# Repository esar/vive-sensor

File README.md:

# vive-sensor
A small PCB implementing this circuit by Alan Yates: https://twitter.com/vk2zay/status/716137353278939136

This circuit amplifies, band-pass filters, and envelope detects the signal received from Vive lighthouse base stations. The output is a clean 3.3V pulse. 

It performs a similar function to the off-the-shelf TS3633-CM1 sensor from Triad Semiconductor, but for a fraction of the cost (and the expense of assembly).

The board is populate on both sides and measures 10mm x 16mm.
The photo-diode can either be a through-hole part mounted as shown in the photo below, or a surface-mount part parallel to the board

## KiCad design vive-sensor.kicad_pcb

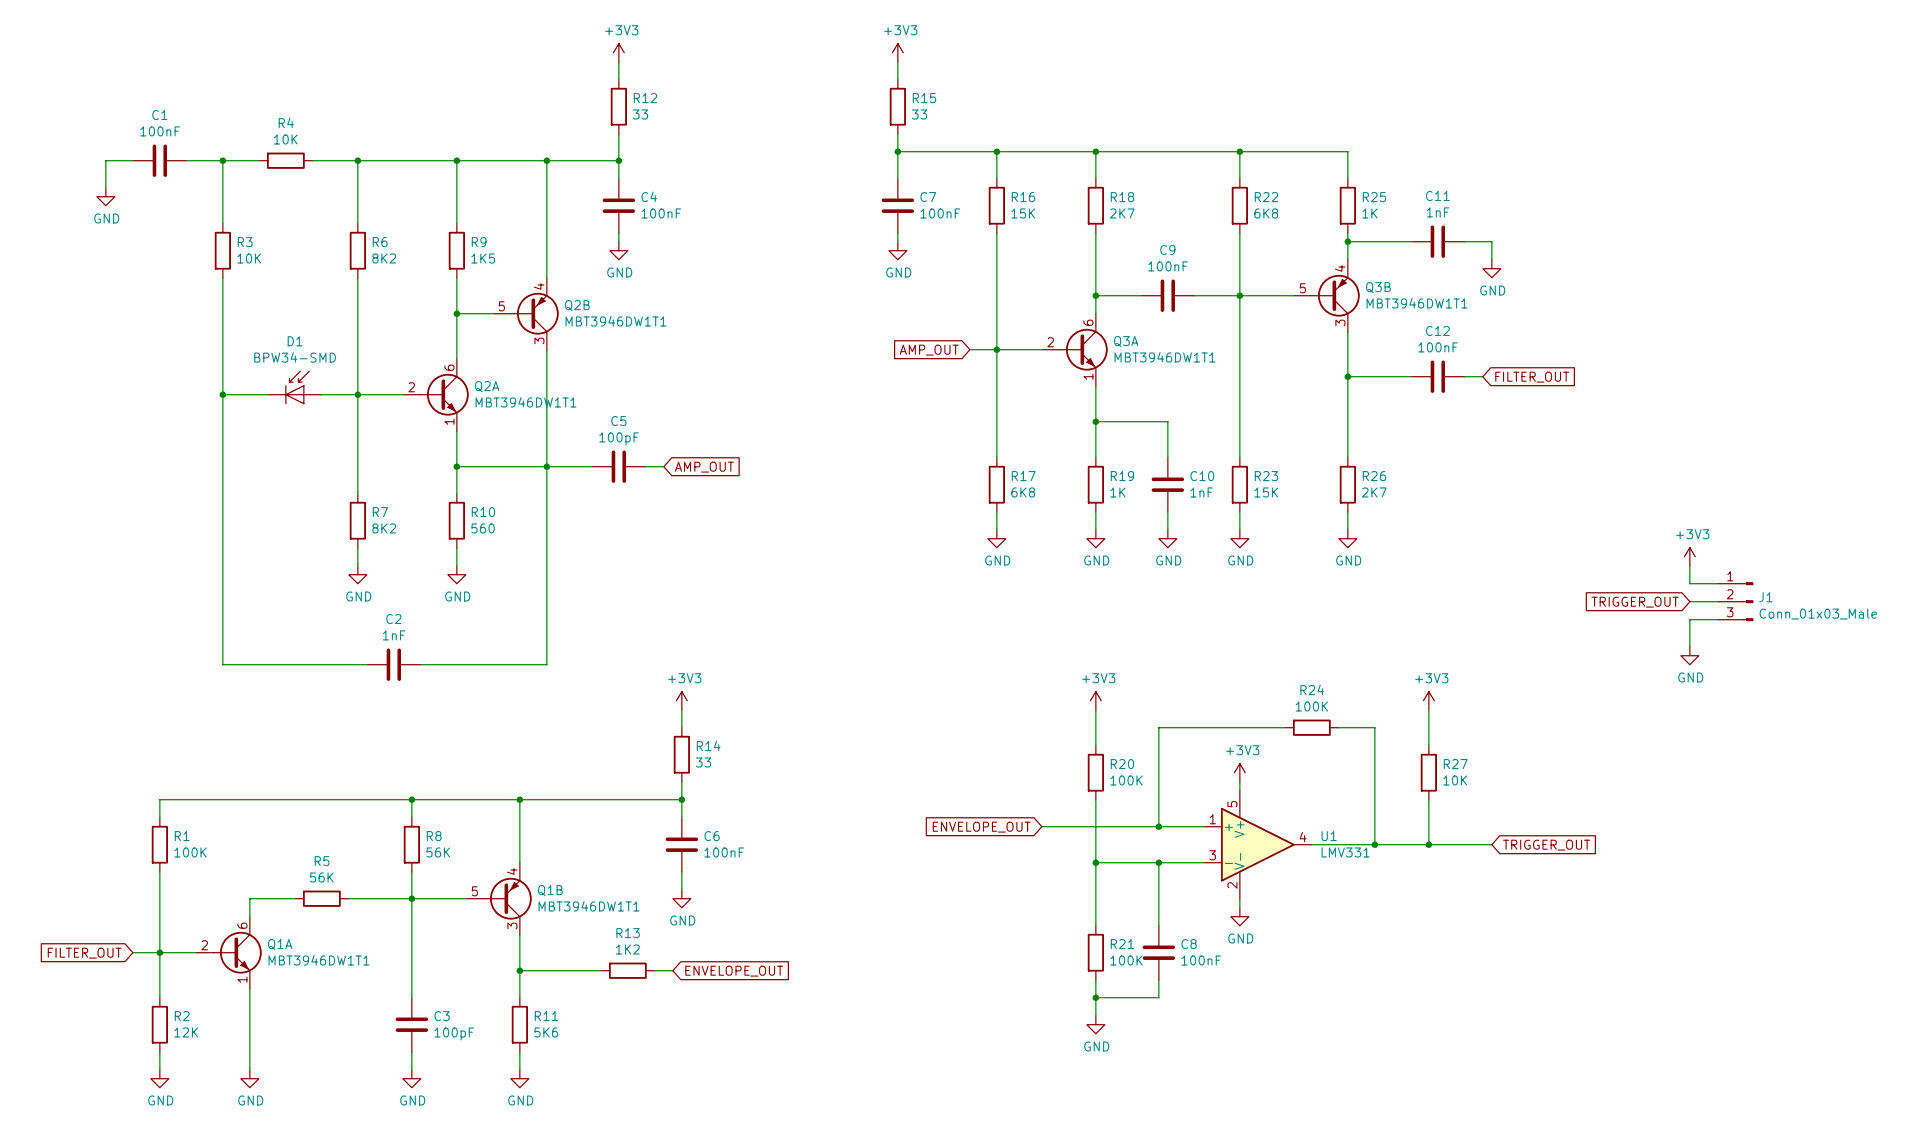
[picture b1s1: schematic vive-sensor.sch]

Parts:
C1, C4, C6, C7, C8, C9, C12: 100nF; C_0402_1005Metric
C2, C10, C11: 1nF; C_0402_1005Metric
C3: 100pF; C_0402_1005Metric
C5: 100pF; C_0603_1608Metric
D1: BPW34-SMD; Osram_SMD-DIL2_4.5x4.0mm
J1: Conn_01x03_Male; PinHeader_1x03_P2.54mm_Vertical
Q1, Q2, Q3: MBT3946DW1T1; SOT-363_SC-70-6
R1, R20, R21, R24: 100K; R_0402_1005Metric
R2: 12K; R_0402_1005Metric
R3, R4, R27: 10K; R_0402_1005Metric
R5, R8: 56K; R_0402_1005Metric
R6, R7: 8K2; R_0402_1005Metric
R9: 1K5; R_0402_1005Metric
R10: 560; R_0402_1005Metric
R11: 5K6; R_0402_1005Metric
R12, R14, R15: 33; R_0402_1005Metric
R13: 1K2; R_0603_1608Metric
R16, R23: 15K; R_0402_1005Metric
R17, R22: 6K8; R_0402_1005Metric
R18, R26: 2K7; R_0402_1005Metric
R19, R25: 1K; R_0402_1005Metric
U1: LMV331; SOT-353_SC-70-5

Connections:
+3V3: J1.1, R12.1, R14.1, R15.1, R20.1, R27.1, U1.5 (V+)
AMP_OUT: C5.1, Q3.2 (B1), R16.2, R17.1
ENVELOPE_OUT: R13.1, R24.2, U1.1 (+)
FILTER_OUT: C12.1, Q1.2 (B1), R1.2, R2.1
GND: C1.2, C3.2, C4.2, C6.2, C7.2, C8.2, C10.2, C11.1, J1.3, Q1.1 (E1), R2.2, R7.2, R10.2, R11.2, R17.2, R19.2, R21.2, R23.2, R26.2, U1.2 (V-)
unnamed: C1.1, R3.1, R4.2
unnamed: C2.1, C5.2, Q2.1 (E1), Q2.3 (C2), R10.1
unnamed: C2.2, D1.1 (K), R3.2
unnamed: C3.1, Q1.5 (B2), R5.1, R8.2
unnamed: C4.1, Q2.4 (E2), R4.1, R6.1, R9.1, R12.2
unnamed: C6.1, Q1.4 (E2), R1.1, R8.1, R14.2
unnamed: C7.1, R15.2, R16.1, R18.1, R22.1, R25.1
unnamed: C8.1, R20.2, R21.1, U1.3 (-)
unnamed: C9.1, Q3.5 (B2), R22.2, R23.1
unnamed: C9.2, Q3.6 (C1), R18.2
unnamed: C10.1, Q3.1 (E1), R19.1
unnamed: C11.2, Q3.4 (E2), R25.2
unnamed: C12.2, Q3.3 (C2), R26.1
unnamed: D1.2 (A), Q2.2 (B1), R6.2, R7.1
unnamed: Q1.3 (C2), R11.1, R13.2
unnamed: Q1.6 (C1), R5.2
unnamed: Q2.5 (B2), Q2.6 (C1), R9.2
TRIGGER_OUT: J1.2, R24.1, R27.2, U1.4

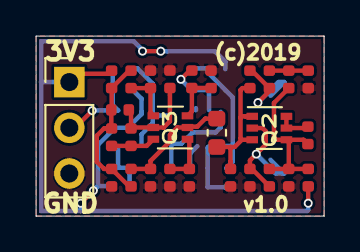
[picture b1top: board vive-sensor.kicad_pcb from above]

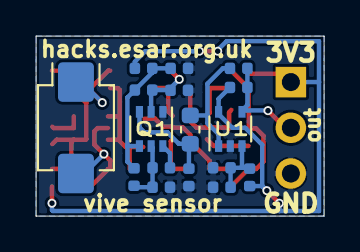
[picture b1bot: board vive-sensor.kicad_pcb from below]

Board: 2 copper layers, 16.0 x 10.0 mm, 45 parts (17 on the bottom side), 23 nets.

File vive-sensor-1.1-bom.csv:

Id,Designator,Package,Quantity,Designation,Supplier and ref
1,"Q2,Q1,Q3",SOT-363_SC-70-6,3,MBT3946DW1T1,Farnell: 1459079
2,"R6,R7",R_0402_1005Metric,2,8K2,
3,"C1,C4,C6,C7,C8,C9,C12",C_0402_1005Metric,7,100nF,
4,"C2,C10,C11",C_0402_1005Metric,3,1nF,
5,C3,C_0402_1005Metric,1,100pF,
6,D1,Osram_SMD-DIL2_4.5x4.0mm,1,BPW34-SMD,Farnell: 1212745
7,"R1,R20,R21,R24",R_0402_1005Metric,4,100K,
8,R2,R_0402_1005Metric,1,12K,
9,"R3,R4,R27",R_0402_1005Metric,3,10K,
10,"R5,R8",R_0402_1005Metric,2,56K,
11,R9,R_0402_1005Metric,1,1K5,
12,R10,R_0402_1005Metric,1,560,
13,R11,R_0402_1005Metric,1,5K6,
14,"R12,R14,R15",R_0402_1005Metric,3,33,
15,"R17,R22",R_0402_1005Metric,2,6K8,
16,"R18,R26",R_0402_1005Metric,2,2K7,
17,"R19,R25",R_0402_1005Metric,2,1K,
18,"R23,R16",R_0402_1005Metric,2,15K,
19,U1,SOT-363_SC-70-6,1,LMV331,Farnell: 2464733
20,J1,PinHeader_1x03_P2.54mm_Vertical,1,Conn_01x03_Male,
21,R13,R_0603_1608Metric,1,1K2,
22,C5,C_0603_1608Metric,1,100pF,

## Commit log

2020-05-09 add v1.1 BOM

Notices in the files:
vive-sensor.kicad_pcb:
(c)2019
